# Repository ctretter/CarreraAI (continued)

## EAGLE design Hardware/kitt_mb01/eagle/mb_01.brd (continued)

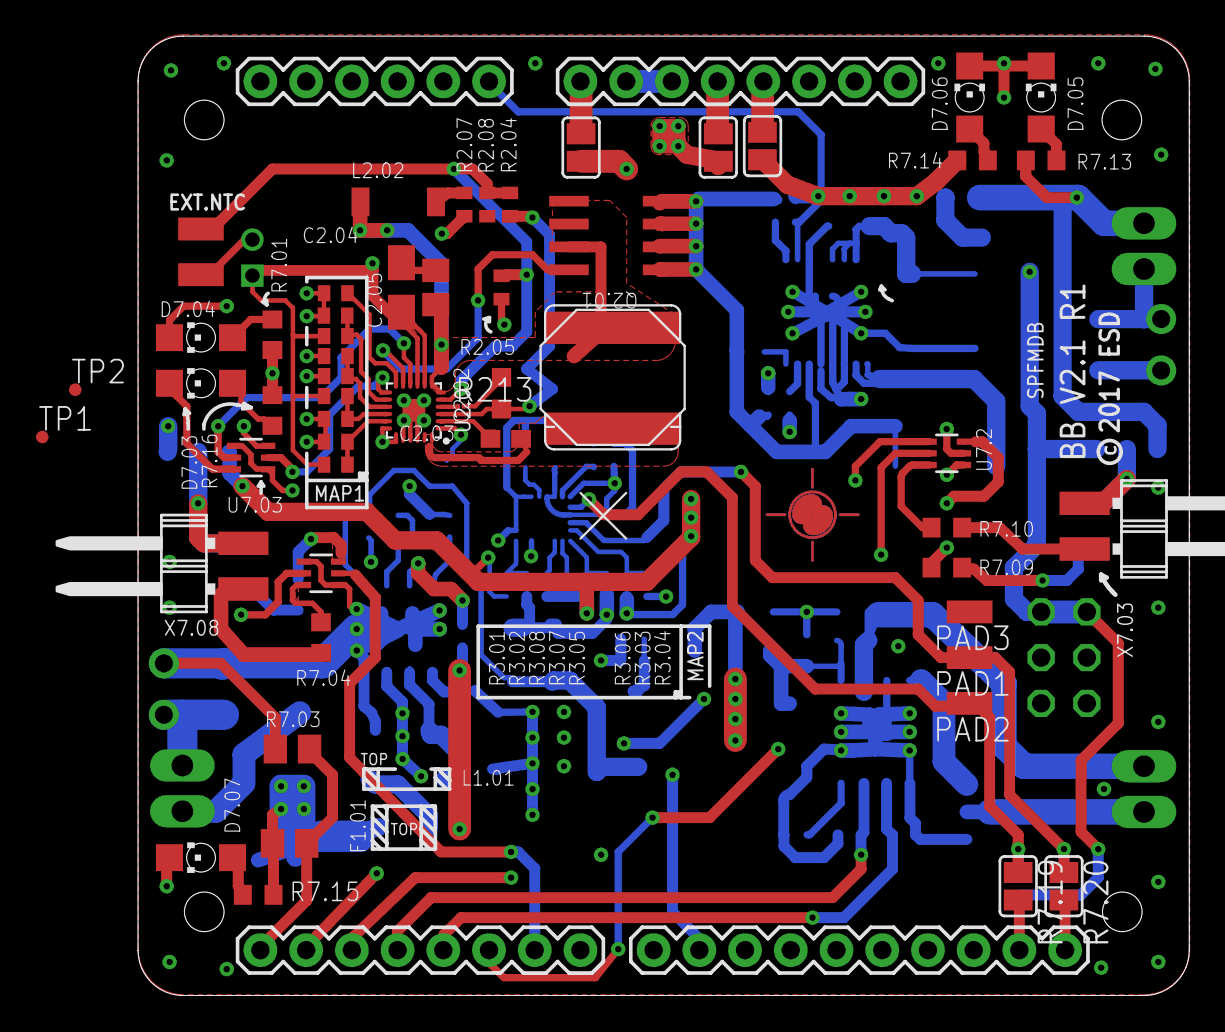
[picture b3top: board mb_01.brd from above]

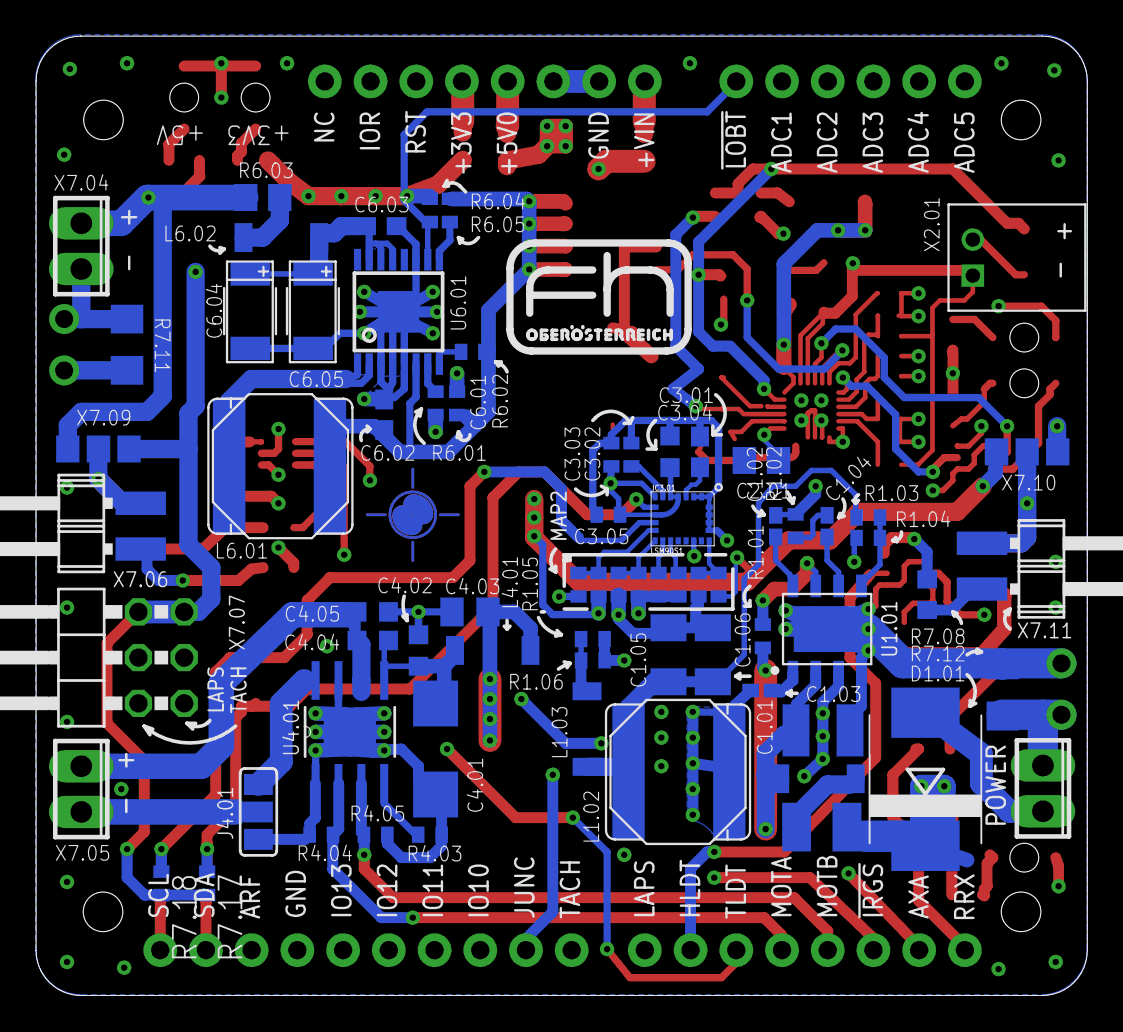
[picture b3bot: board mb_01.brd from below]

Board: 8 copper layers, 58.4 x 53.3 mm, 132 parts (73 on the bottom side), 88 nets.

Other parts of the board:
R213: [10k]; R01005
TP1, TP2: TPTP07R; TP07R
U2.0: BQ24266RGET; VQFN-24
U$3: A4L-LOC
U$5: PASS-ROUND
U$8: PASSER-CIRCLE

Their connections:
+4.1V: U2.0.8, U2.0.9; also elsewhere on the board
+5V: U2.0.18, U2.0.19; also elsewhere on the board
GND: R213.2, U2.0.20, U2.0.21, U2.0.22, U2.0.PAD; also elsewhere on the board
IC2.0.!CHG: U2.0.13; also elsewhere on the board
IC2.0.!PG: U2.0.10; also elsewhere on the board
unnamed: R213.1, U2.0.4
unnamed 30: U2.0.15; also elsewhere on the board
unnamed 33: U2.0.12; also elsewhere on the board
unnamed 34: U2.0.17; also elsewhere on the board
unnamed 35: U2.0.16; also elsewhere on the board
unnamed 36: U2.0.14; also elsewhere on the board
U2.0/BGATE: U2.0.11; also elsewhere on the board
U2.0/BOOT: U2.0.2; also elsewhere on the board
U2.0/DRV: U2.0.3; also elsewhere on the board
U2.0/PMID: U2.0.1; also elsewhere on the board
U2.0/SW: U2.0.23, U2.0.24; also elsewhere on the board
U2.0/SYS: U2.0.6, U2.0.7; also elsewhere on the board
U2.0/TS: U2.0.5; also elsewhere on the board

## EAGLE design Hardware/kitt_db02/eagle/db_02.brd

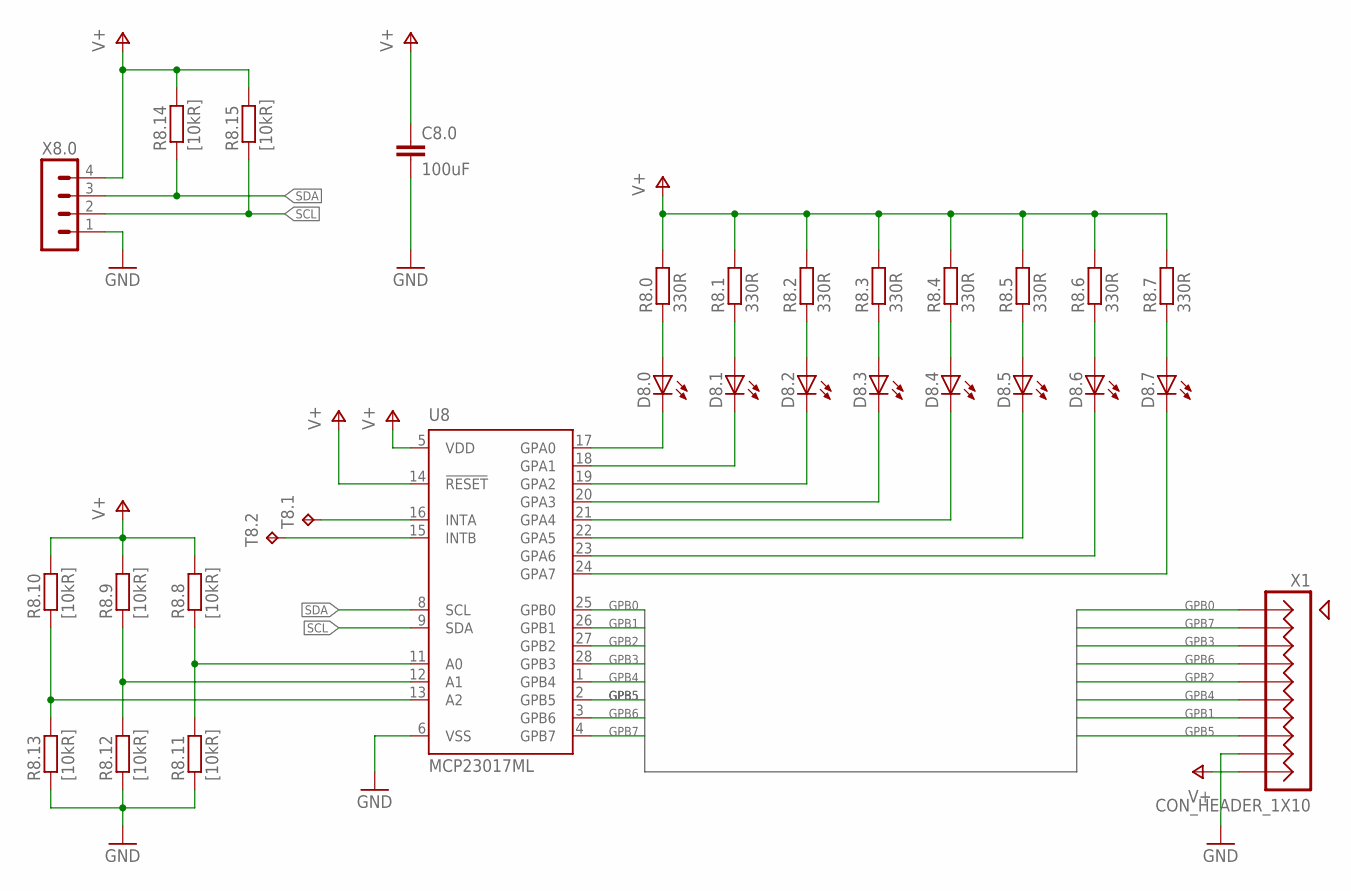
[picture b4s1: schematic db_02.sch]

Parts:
C8.0: 100uF; C0603
D8.0, D8.1, D8.2, D8.3, D8.4, D8.5, D8.6, D8.7: LEDCHIPLED_1206; CHIPLED_1206
R8.0, R8.1, R8.2, R8.3, R8.4, R8.5, R8.6, R8.7: 330R; R0603
R8.8, R8.9, R8.10, R8.11, R8.12, R8.13, R8.14, R8.15: [10kR]; R0402
T8.1, T8.2: TPTP09SQ; TP09SQ
U8: MCP23017ML; QFN28-ML_6X6MM
X1: CON_HEADER_1X10; M1X10_SMD
X8.0: MA04-1

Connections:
GND: C8.0.2, R8.11.1, R8.12.1, R8.13.1, U8.6 (VSS), X1.P$9, X8.0.1
GPB0: U8.25 (GPB0), X1.P$1
GPB1: U8.26 (GPB1), X1.P$7
GPB2: U8.27 (GPB2), X1.P$5
GPB3: U8.28 (GPB3), X1.P$3
GPB4: U8.1 (GPB4), X1.P$6
GPB5: U8.2 (GPB5), X1.P$8
GPB6: U8.3 (GPB6), X1.P$4
GPB7: U8.4 (GPB7), X1.P$2
unnamed: D8.0.C, U8.17 (GPA0)
unnamed: D8.1.C, U8.18 (GPA1)
unnamed: D8.2.C, U8.19 (GPA2)
unnamed: D8.3.C, U8.20 (GPA3)
unnamed: D8.4.C, U8.21 (GPA4)
unnamed: D8.5.C, U8.22 (GPA5)
unnamed: D8.6.C, U8.23 (GPA6)
unnamed: D8.7.C, U8.24 (GPA7)
unnamed: D8.0.A, R8.0.1
unnamed: D8.1.A, R8.1.1
unnamed: D8.2.A, R8.2.1
unnamed: D8.3.A, R8.3.1
unnamed: D8.4.A, R8.4.1
unnamed: D8.5.A, R8.5.1
unnamed: D8.6.A, R8.6.1
unnamed: D8.7.A, R8.7.1
unnamed: R8.8.1, R8.11.2, U8.11 (A0)
unnamed: R8.9.1, R8.12.2, U8.12 (A1)
unnamed: R8.10.1, R8.13.2, U8.13 (A2)
unnamed: T8.1.TP, U8.16 (INTA)
unnamed: T8.2.TP, U8.15 (INTB)
SCL: R8.15.1, U8.9 (SDA), X8.0.2
SDA: R8.14.1, U8.8 (SCL), X8.0.3
V+: C8.0.1, R8.0.2, R8.1.2, R8.2.2, R8.3.2, R8.4.2, R8.5.2, R8.6.2, R8.7.2, R8.8.2, R8.9.2, R8.10.2, R8.14.2, R8.15.2, U8.5 (VDD), U8.14 (!RESET), X1.P$10, X8.0.4

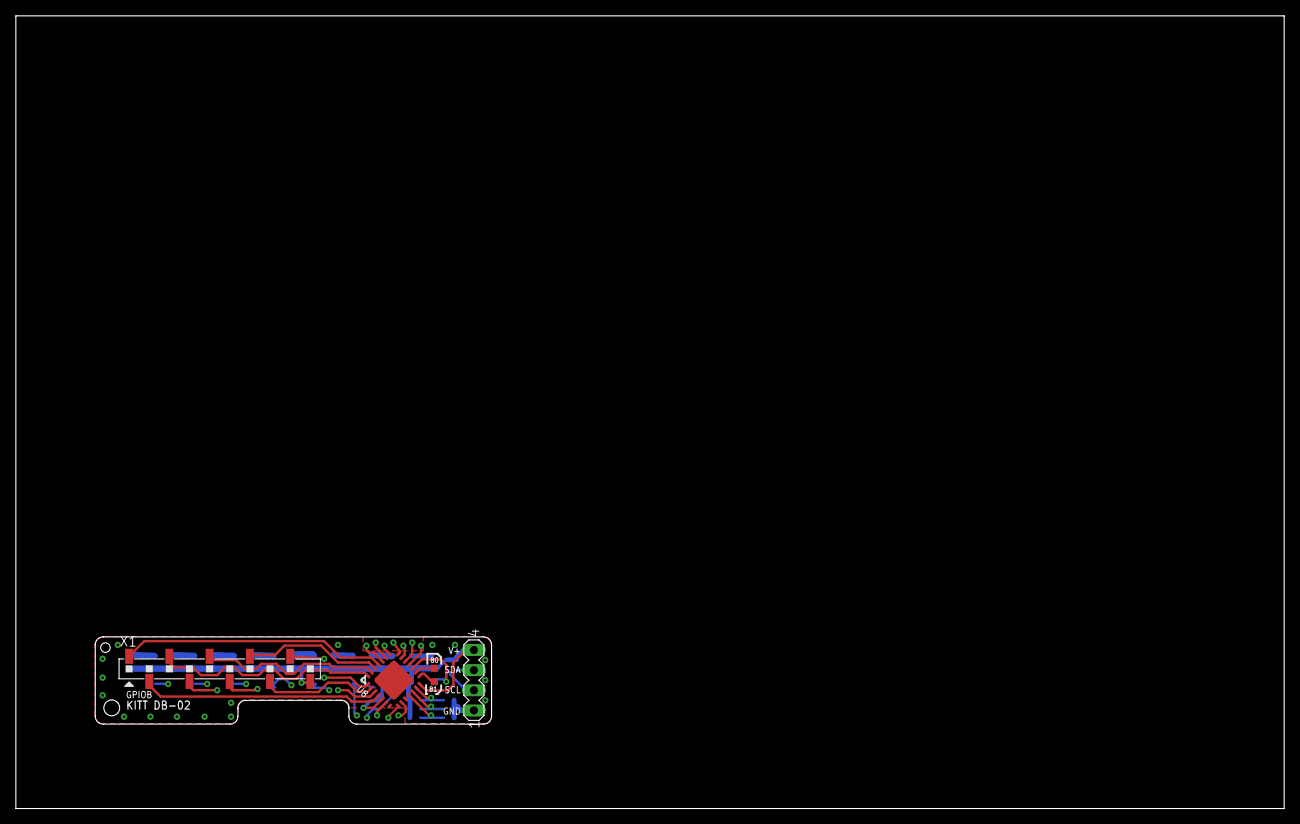
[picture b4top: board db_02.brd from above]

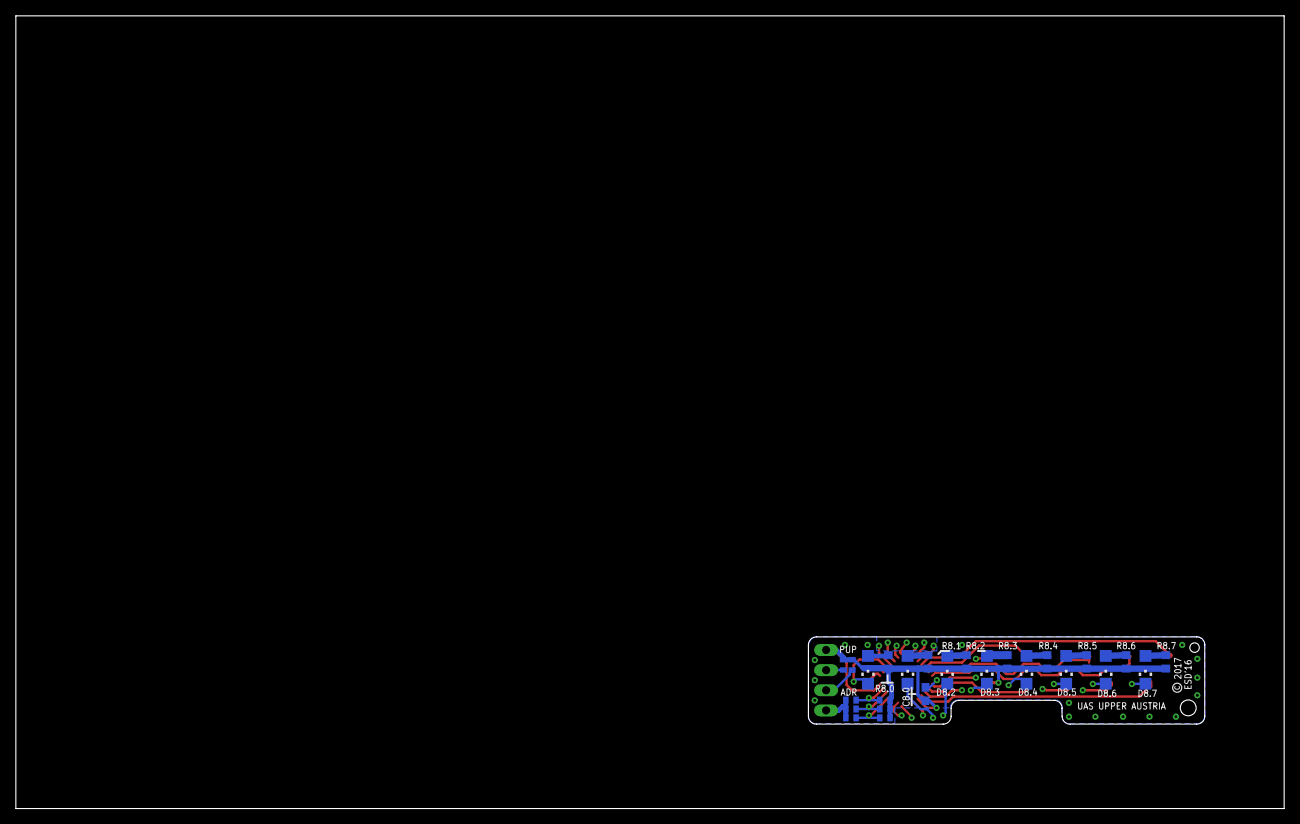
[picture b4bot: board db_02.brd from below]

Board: 8 copper layers, 160.0 x 100.0 mm, 30 parts (25 on the bottom side), 33 nets.

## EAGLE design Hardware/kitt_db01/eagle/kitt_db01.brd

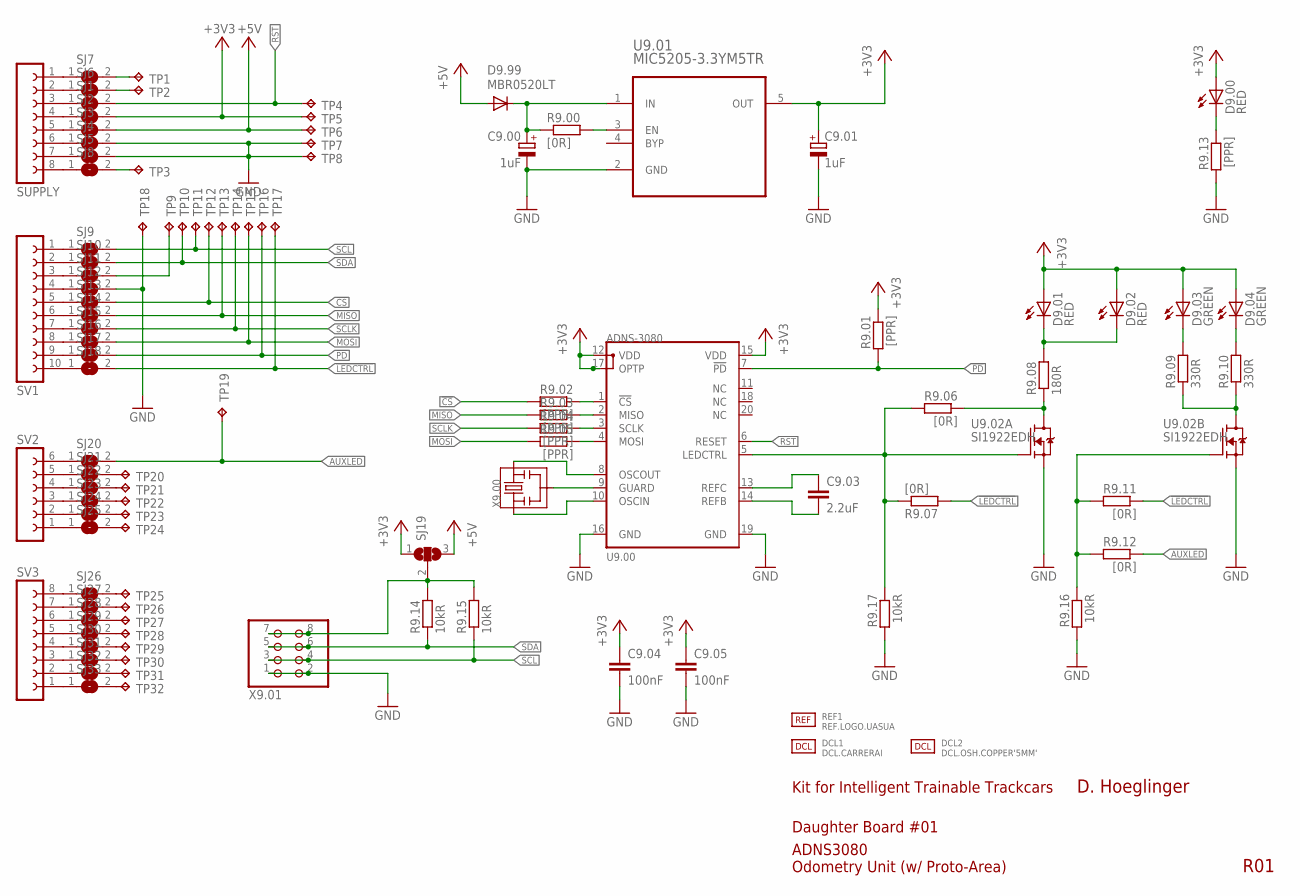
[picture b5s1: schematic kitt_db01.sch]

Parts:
C9.00, C9.01: 1uF; A/3216-18W
C9.03: 2.2uF; C1608
C9.04, C9.05: 100nF; C0805K
D9.00, D9.02: RED; CHIP-LED0805
D9.01: RED; LED5MM
D9.03, D9.04: GREEN; CHIP-LED0805
D9.99: MBR0520LT; SOD123
DCL1: DCL.CARRERAI; DCL.LOGO-CARRERAI.W30MM
DCL2: DCL.OSH.COPPER'5MM'; DCL.LOGO-OSH.5MM
R9.00, R9.06, R9.07, R9.11, R9.12: [0R]; R0805
R9.01, R9.02, R9.03, R9.04, R9.05, R9.13: [PPR]; R0805
R9.08: 180R; R0805
R9.09, R9.10: 330R; R0805
R9.14, R9.15, R9.16, R9.17: 10kR; R0805
REF1: REF.LOGO.UASUA; REF_LOGO_UASUA
SJ1, SJ2, SJ3, SJ4, SJ5, SJ6, SJ7, SJ8, SJ9, SJ10, SJ11, SJ12, SJ13, SJ14, SJ15, SJ16, SJ17, SJ18, SJ20, SJ21, SJ22, SJ23, SJ24, SJ25, SJ26, SJ27, SJ28, SJ29, SJ30, SJ31, SJ32, SJ33: SJ
SJ19: SJ2W; SJ_2
SUPPLY: FE08-1; FE08
SV1: FE10-1; FE10
SV2: FE06-1; FE06
SV3: FE08-1; FE08
TP1, TP2, TP3, TP4, TP5, TP6, TP7, TP8, TP9, TP10, TP11, TP12, TP13, TP14, TP15, TP16, TP17, TP18, TP19, TP20, TP21, TP22, TP23, TP24, TP25, TP26, TP27, TP28, TP29, TP30, TP31, TP32: TPPAD1-13; P1-13
U9.00: ADNS-3080
U9.01: MIC5205-3.3YM5TR; SOT95P280X130-5N
U9.02: SI1922EDH; SC70-6
X9.00: RESON; RESON-SMD
X9.01: PINHD-2X4/90; 2X04/90

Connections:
!CS: R9.02.2, SJ13.2, TP12.TP
!LEDCTRL: R9.07.2, R9.11.1, SJ18.2, TP17.TP
!PD: R9.01.2, SJ17.2, TP16.TP, U9.00.7 (!PD)
+3V3: C9.01.+, C9.04.1, C9.05.1, D9.00.A, D9.01.A, D9.02.A, D9.03.A, D9.04.A, R9.01.1, SJ2.2, SJ19.1, TP5.TP, U9.00.12 (VDD), U9.00.15 (VDD), U9.00.17 (OPTP), U9.01.5 (OUT)
+5V: D9.99.A, SJ3.2, SJ19.3, TP6.TP
AUXLED: R9.12.1, SJ20.2, TP19.TP
GND: C9.00.-, C9.01.-, C9.04.2, C9.05.2, R9.13.2, R9.16.2, R9.17.2, SJ4.2, SJ5.2, SJ12.2, TP7.TP, TP8.TP, TP18.TP, U9.00.16 (GND), U9.00.19 (GND), U9.01.2 (GND), U9.02.1 (S), U9.02.4 (S), X9.01.1, X9.01.2
MISO: R9.03.2, SJ14.2, TP13.TP
MOSI: R9.05.2, SJ16.2, TP15.TP
unnamed: U9.00.9 (GUARD), X9.00.2
unnamed: U9.00.8 (OSCOUT), X9.00.3
unnamed: U9.00.10 (OSCIN), X9.00.1
unnamed: R9.06.2, R9.07.1, R9.17.1, U9.00.5 (LEDCTRL), U9.02.2 (G)
unnamed: C9.03.1, U9.00.13 (REFC)
unnamed: C9.03.2, U9.00.14 (REFB)
unnamed: R9.06.1, R9.08.1, U9.02.6 (D)
unnamed: D9.01.K (C), D9.02.C, R9.08.2
unnamed: C9.00.+, D9.99.C, R9.00.1, U9.01.1 (IN)
unnamed: R9.00.2, U9.01.3 (EN)
unnamed: D9.00.C, R9.13.1
unnamed: SJ1.1, SUPPLY.3
unnamed: SJ2.1, SUPPLY.4
unnamed: R9.14.2, R9.15.2, SJ19.2, X9.01.7, X9.01.8
unnamed: SJ3.1, SUPPLY.5
unnamed: SJ4.1, SUPPLY.6
unnamed: SJ5.1, SUPPLY.7
unnamed: SJ7.1, SUPPLY.1
unnamed: SJ6.1, SUPPLY.2
unnamed: SJ8.1, SUPPLY.8
unnamed: SJ7.2, TP1.TP
unnamed: SJ6.2, TP2.TP
unnamed: SJ8.2, TP3.TP
unnamed: SJ9.1, SV1.1
unnamed: SJ10.1, SV1.2
unnamed: SJ11.1, SV1.3
unnamed: SJ11.2, TP9.TP
unnamed: SJ12.1, SV1.4
unnamed: SJ13.1, SV1.5
unnamed: SJ14.1, SV1.6
unnamed: SJ15.1, SV1.7
unnamed: SJ16.1, SV1.8
unnamed: SJ17.1, SV1.9
unnamed: SJ18.1, SV1.10
unnamed: SJ20.1, SV2.6
unnamed: SJ21.1, SV2.5
unnamed: SJ22.1, SV2.4
unnamed: SJ23.1, SV2.3
unnamed: SJ24.1, SV2.2
unnamed: SJ25.1, SV2.1
unnamed: SJ26.1, SV3.8
unnamed: SJ27.1, SV3.7
unnamed: SJ28.1, SV3.6
unnamed: SJ29.1, SV3.5
unnamed: SJ30.1, SV3.4
unnamed: SJ31.1, SV3.3
unnamed: SJ32.1, SV3.2
unnamed: SJ33.1, SV3.1
unnamed: R9.02.1, U9.00.1 (!CS)
unnamed: SJ21.2, TP20.TP
unnamed: SJ22.2, TP21.TP
unnamed: SJ23.2, TP22.TP
unnamed: SJ24.2, TP23.TP
unnamed: SJ25.2, TP24.TP
unnamed: SJ26.2, TP25.TP
unnamed: SJ27.2, TP26.TP
unnamed: SJ28.2, TP27.TP
unnamed: SJ29.2, TP28.TP
unnamed: SJ30.2, TP29.TP
unnamed: SJ31.2, TP30.TP
unnamed: SJ32.2, TP31.TP
unnamed: SJ33.2, TP32.TP
unnamed: R9.03.1, U9.00.2 (MISO)
unnamed: R9.04.1, U9.00.3 (SCLK)
unnamed: R9.11.2, R9.12.2, R9.16.1, U9.02.5 (G)
unnamed: D9.04.C, R9.10.2
unnamed: R9.09.1, R9.10.1, U9.02.3 (D)
unnamed: D9.03.C, R9.09.2
unnamed: R9.05.1, U9.00.4 (MOSI)
RST: SJ1.2, TP4.TP, U9.00.6 (RESET)
SCL: R9.15.1, SJ9.2, TP11.TP, X9.01.3, X9.01.4
SCLK: R9.04.2, SJ15.2, TP14.TP
SDA: R9.14.1, SJ10.2, TP10.TP, X9.01.5, X9.01.6

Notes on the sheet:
Kit for Intelligent Trainable Trackcars
Daughter Board #01
ADNS3080 Odometry Unit (w/ Proto-Area)
R01
D. Hoeglinger

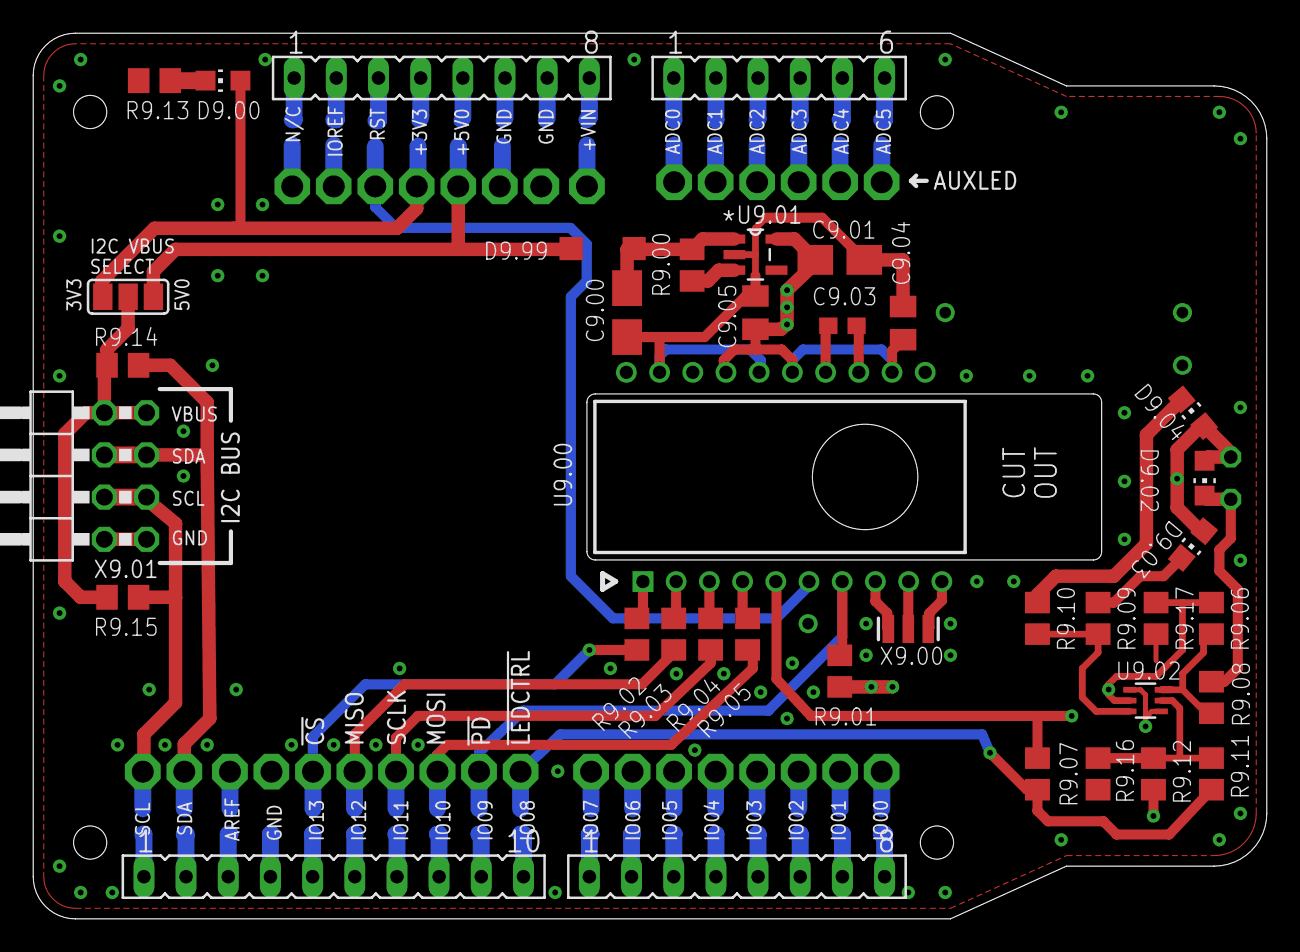
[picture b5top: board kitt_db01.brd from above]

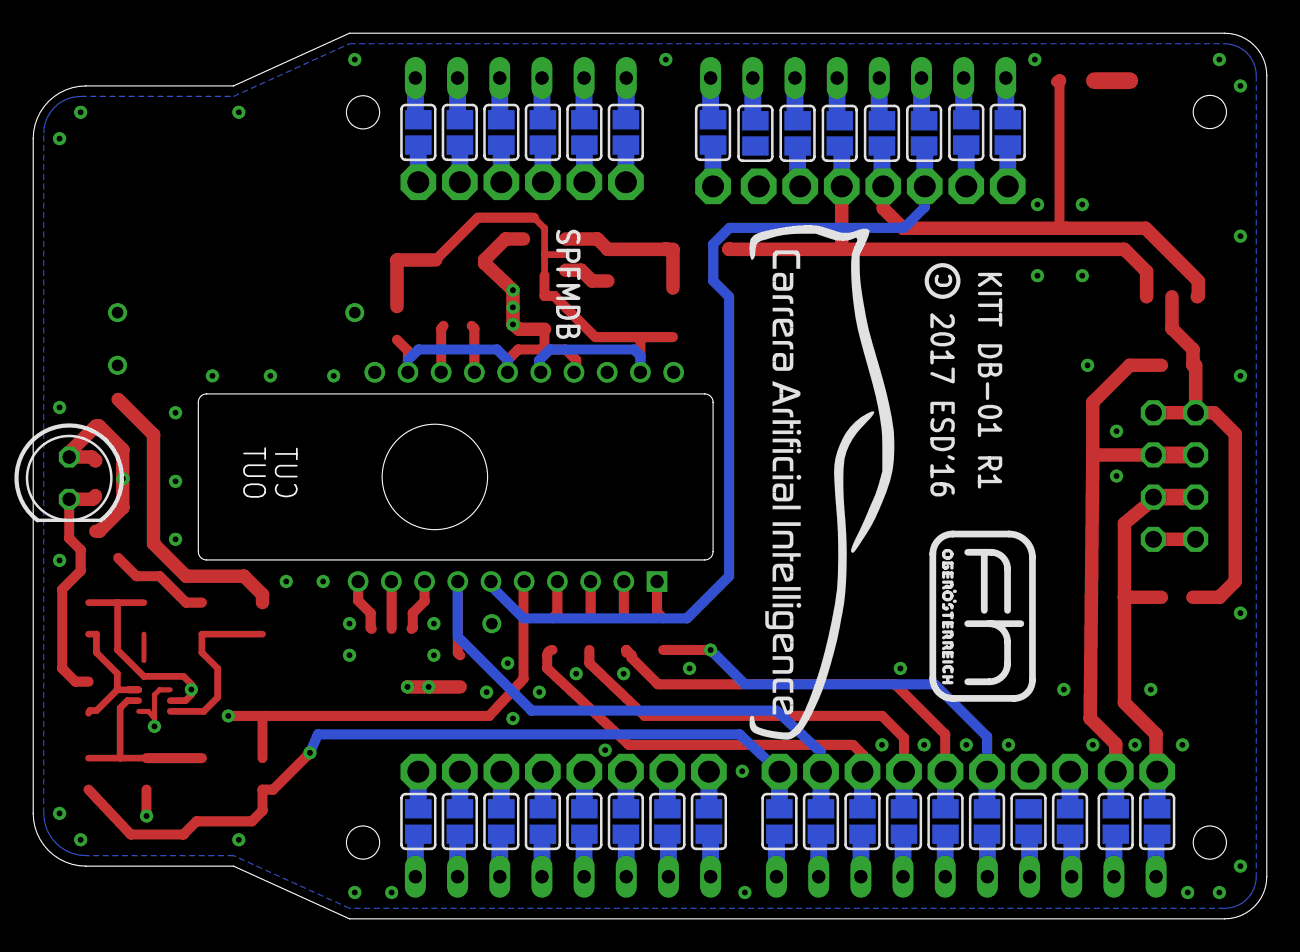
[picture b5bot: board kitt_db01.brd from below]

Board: 8 copper layers, 74.3 x 53.3 mm, 107 parts (36 on the bottom side), 82 nets.

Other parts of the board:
U$2: A4L-LOC

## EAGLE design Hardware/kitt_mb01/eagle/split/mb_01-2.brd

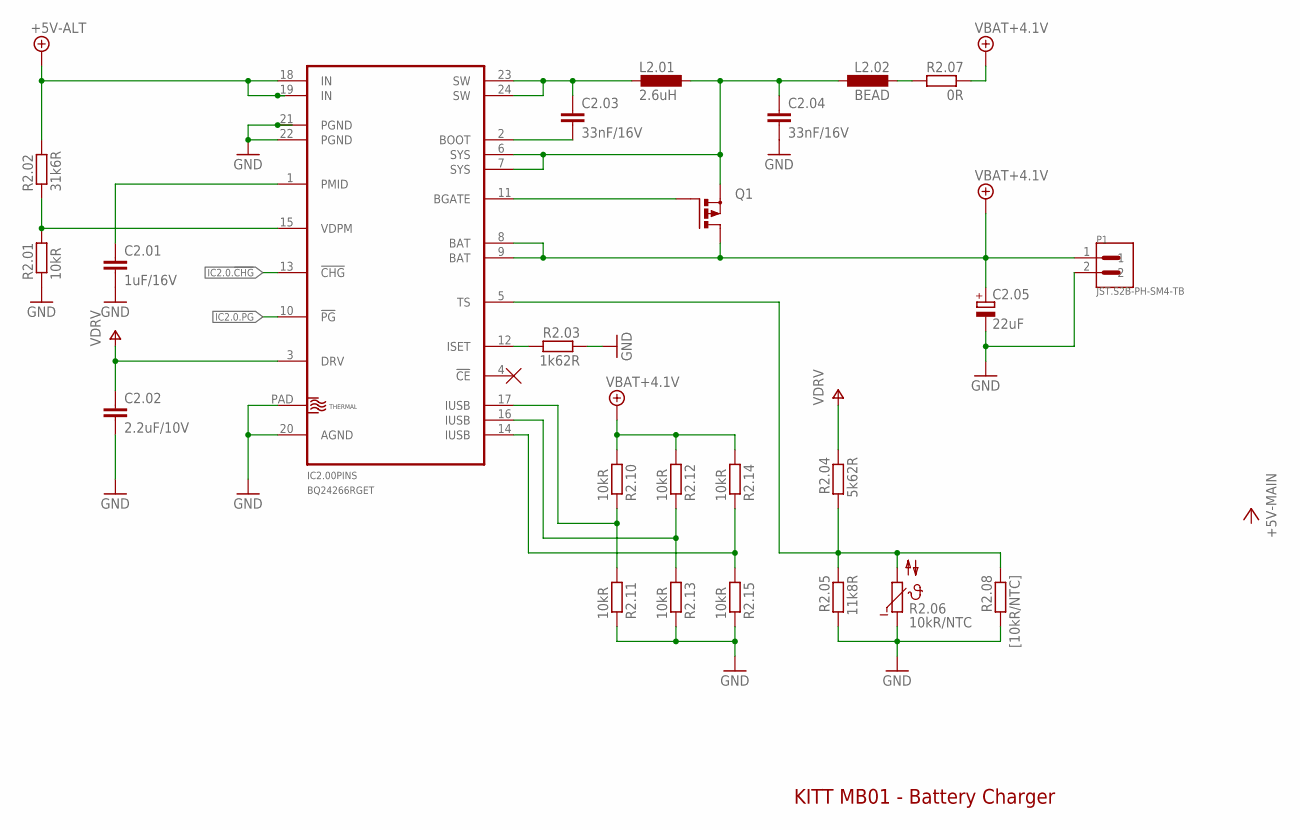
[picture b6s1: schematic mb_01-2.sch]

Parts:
C2.01: 1uF/16V; C0805
C2.02: 2.2uF/10V; C0603K
C2.03: 33nF/16V; C0603
C2.04: 33nF/16V; C0805
C2.05: 22uF; A/3216-18R
IC2.00: BQ24266RGET; VQFN-24
L2.01: 2.6uH; POWER-CHOKE_WE-TPC
L2.02: BEAD; L2012C
P1: JST.S2B-PH-SM4-TB; JST_S2B-PH-SM4-TB(LF)(SN)
Q1: P-MOSFET-SO8; SO-08
R2.01, R2.10, R2.11, R2.12, R2.13, R2.14, R2.15: 10kR; R0402
R2.02: 31k6R; R0402
R2.03: 1k62R; R0402
R2.04: 5k62R; R0402
R2.05: 11k8R; R0402
R2.06: 10kR/NTC; P642
R2.07: 0R; R0402
R2.08: [10kR/NTC]; R0402

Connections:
+4.1V: C2.05.+, IC2.00.8 (BAT), IC2.00.9 (BAT), P1.1, Q1.5 (D), Q1.6 (D), Q1.7 (D), Q1.8 (D), R2.07.1, R2.10.2, R2.12.2, R2.14.2
+5V: IC2.00.18 (IN), IC2.00.19 (IN), R2.02.2
GND: C2.01.2, C2.02.2, C2.04.2, C2.05.-, IC2.00.20 (AGND), IC2.00.21 (PGND), IC2.00.22 (PGND), IC2.00.PAD (THERMAL), P1.2, R2.01.1, R2.03.1, R2.05.2, R2.06.1, R2.08.2, R2.11.1, R2.13.1, R2.15.1
IC2.0.!CHG: IC2.00.13 (!CHG)
IC2.0.!PG: IC2.00.10 (!PG)
unnamed: C2.01.1, IC2.00.1 (PMID)
unnamed: IC2.00.15 (VDPM), R2.01.2, R2.02.1
unnamed: C2.03.1, IC2.00.23 (SW), IC2.00.24 (SW), L2.01.2
unnamed: C2.03.2, IC2.00.2 (BOOT)
unnamed: IC2.00.11 (BGATE), Q1.4 (G)
unnamed: IC2.00.5 (TS), R2.04.2, R2.05.1, R2.06.2, R2.08.1
unnamed: L2.02.2, R2.07.2
unnamed: C2.04.1, IC2.00.6 (SYS), IC2.00.7 (SYS), L2.01.1, L2.02.1, Q1.1 (S), Q1.2 (S), Q1.3 (S)
unnamed: IC2.00.12 (ISET), R2.03.2
unnamed: IC2.00.17 (IUSB), R2.10.1, R2.11.2
unnamed: IC2.00.16 (IUSB), R2.12.1, R2.13.2
unnamed: IC2.00.14 (IUSB), R2.14.1, R2.15.2
V+: C2.02.1, IC2.00.3 (DRV), R2.04.1

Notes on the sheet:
KITT MB01 - Battery Charger

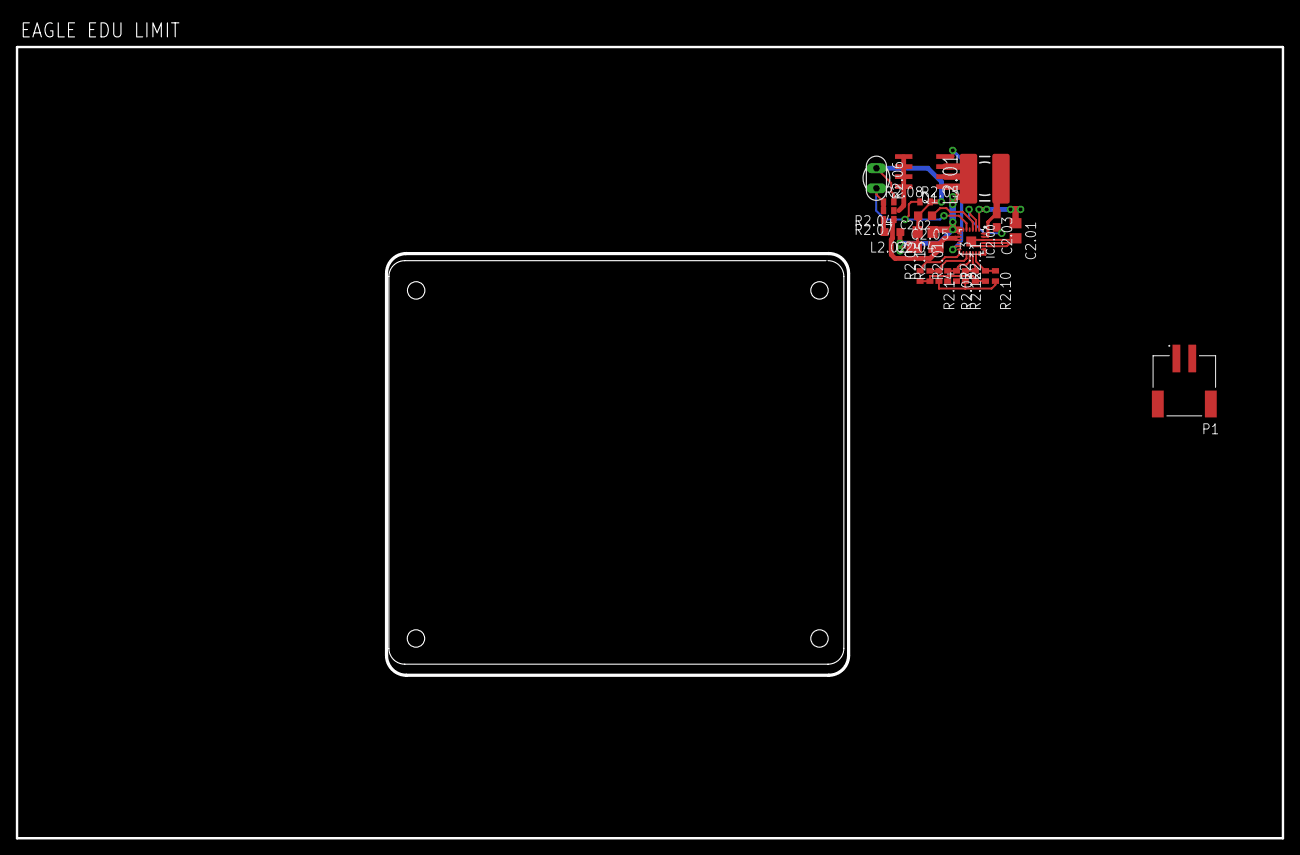
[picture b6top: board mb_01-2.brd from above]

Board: 8 copper layers, 160.0 x 100.0 mm, 24 parts (0 on the bottom side), 16 nets.

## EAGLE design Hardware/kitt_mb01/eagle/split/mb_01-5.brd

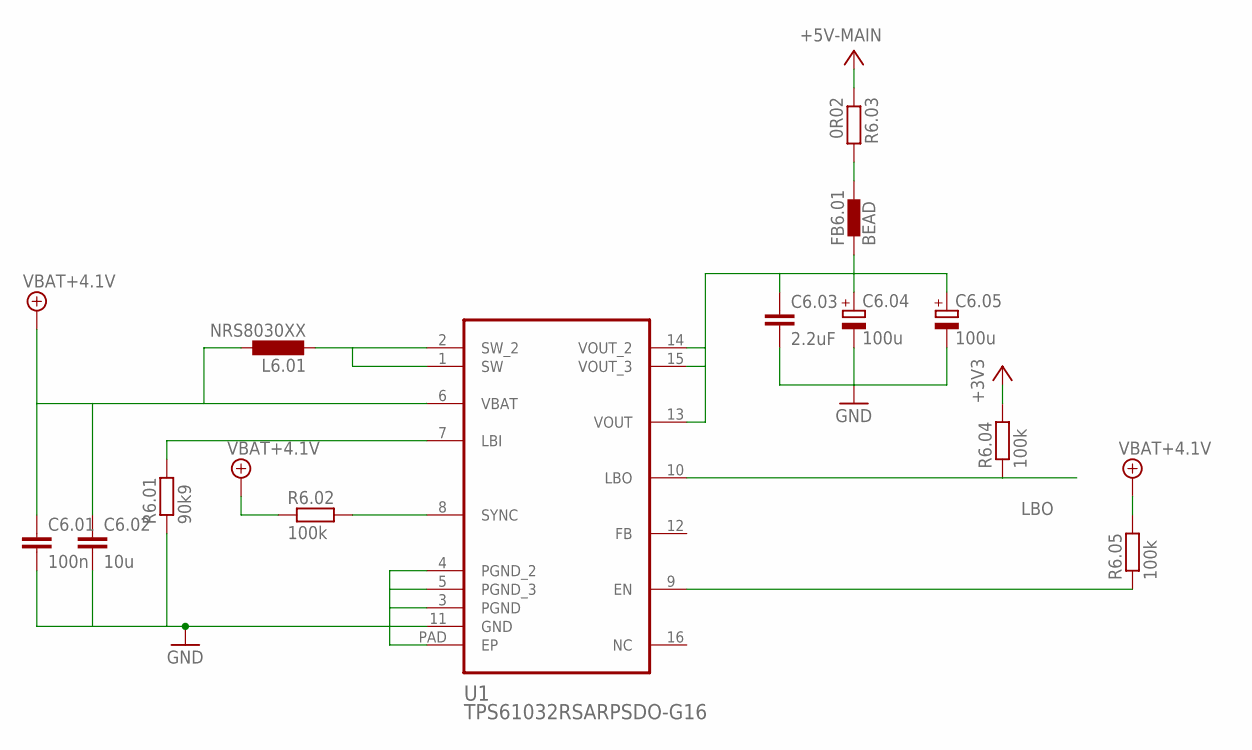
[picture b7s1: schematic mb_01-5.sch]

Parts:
C6.01: 100n; C0402
C6.02: 10u; C0603
C6.03: 2.2uF; C0603
C6.04, C6.05: 100u; C-2312
FB6.01: BEAD; 0402
L6.01: NRS8030XX; TAIYO-YUDEN.NRS8030T4R7MJGJ
R6.01: 90k9; R0402
R6.02, R6.04, R6.05: 100k; R0402
R6.03: 0R02; R0805
U1: TPS61032RSARPSDO-G16; R-PDSO-G16

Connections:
+3V3: R6.04.2
+4.1V: C6.01.1, C6.02.1, L6.01.1, R6.02.1, R6.05.2, U1.6 (VBAT)
+5V: R6.03.1
GND: C6.01.2, C6.02.2, C6.03.2, C6.04.N (-), C6.05.N (-), R6.01.1, U1.3 (PGND), U1.4 (PGND_2), U1.5 (PGND_3), U1.11 (GND), U1.PAD (EP)
LBO: R6.04.1, U1.10 (LBO)
unnamed: FB6.01.2, R6.03.2
unnamed: R6.05.1, U1.9 (EN)
unnamed: L6.01.2, U1.1 (SW), U1.2 (SW_2)
unnamed: R6.01.2, U1.7 (LBI)
unnamed: R6.02.2, U1.8 (SYNC)
unnamed: C6.03.1, C6.04.P (+), C6.05.P (+), FB6.01.1, U1.13 (VOUT), U1.14 (VOUT_2), U1.15 (VOUT_3)

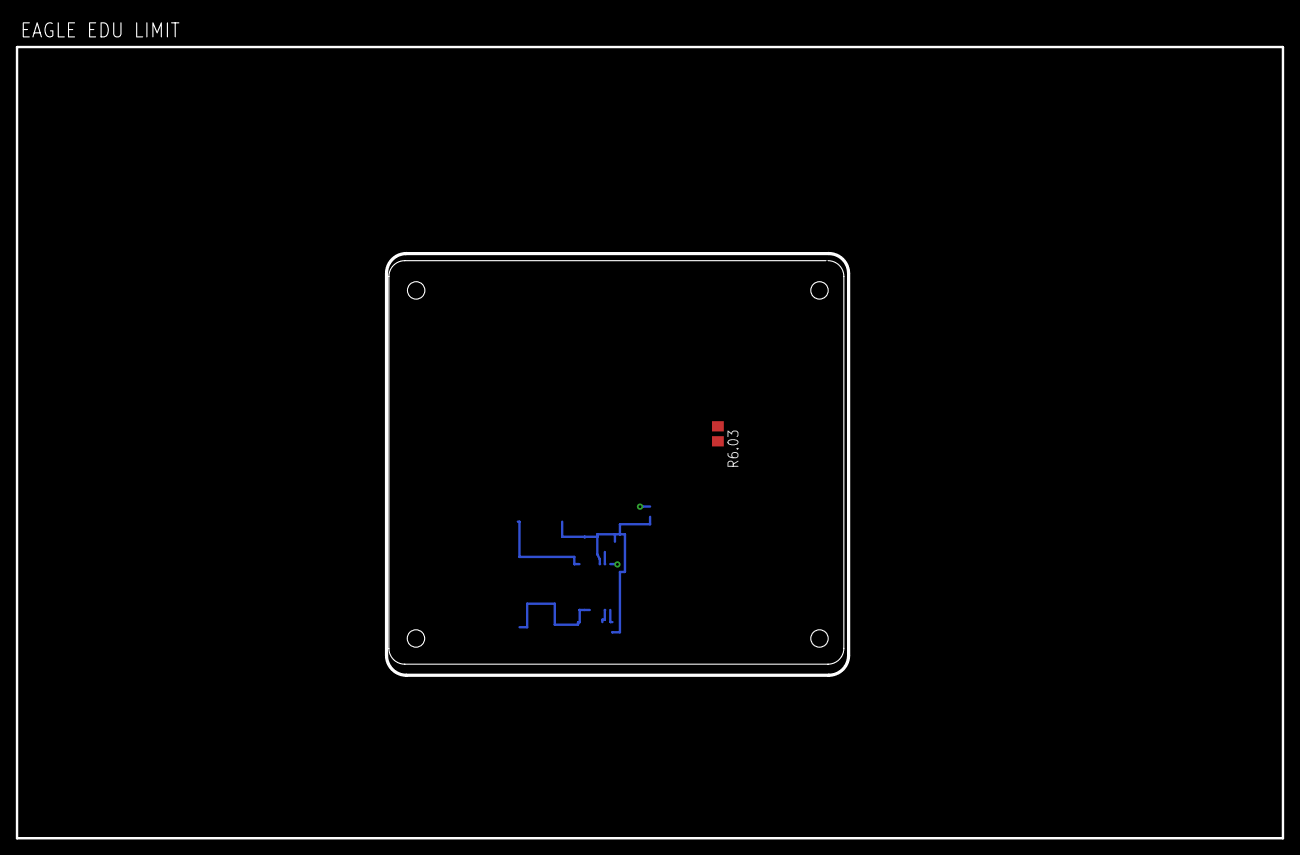
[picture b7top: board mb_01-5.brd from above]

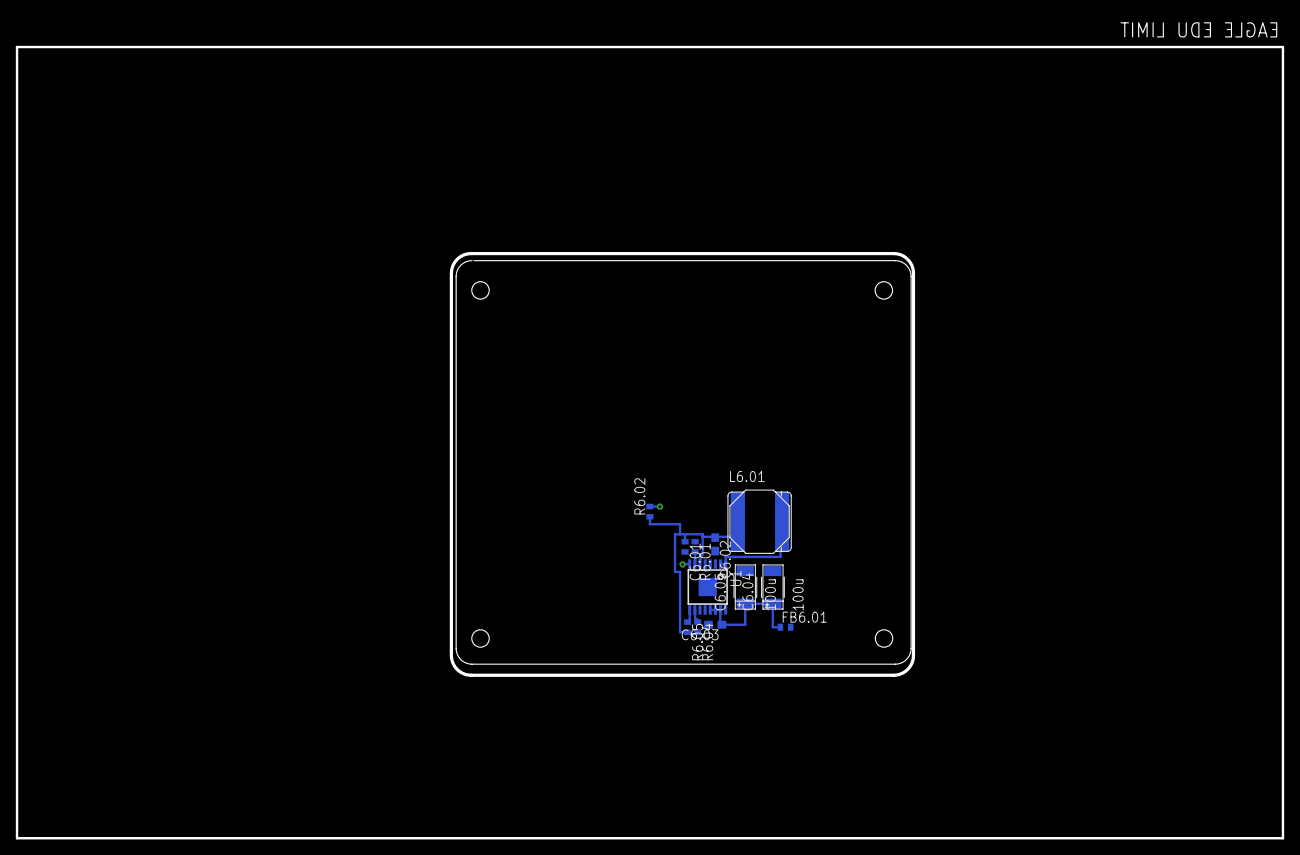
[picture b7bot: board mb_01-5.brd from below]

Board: 8 copper layers, 160.0 x 100.0 mm, 15 parts (13 on the bottom side), 9 nets.

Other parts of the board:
U$1: REF_GCB2_TS
U$2: REF_GCB2_BS
